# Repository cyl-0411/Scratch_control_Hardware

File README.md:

# Scratch_control_Hardware

	`Robotmaster`资源岛的控制器，需要控制一个舵机、一条LED灯带和一个红外传感器。
	
	主控：`STM32G030F6P6`，十分的廉价
	
	舵机：`MG995`

#### 更新日志：

2022/7/23

第一版比较拉，现在第二版准备不用中心板，直接将`MG995`、LED灯带和传感器接到主控板上。

此外会更新丝印，防止反插的情况。

2022/10/1

增加了几个去耦电容。

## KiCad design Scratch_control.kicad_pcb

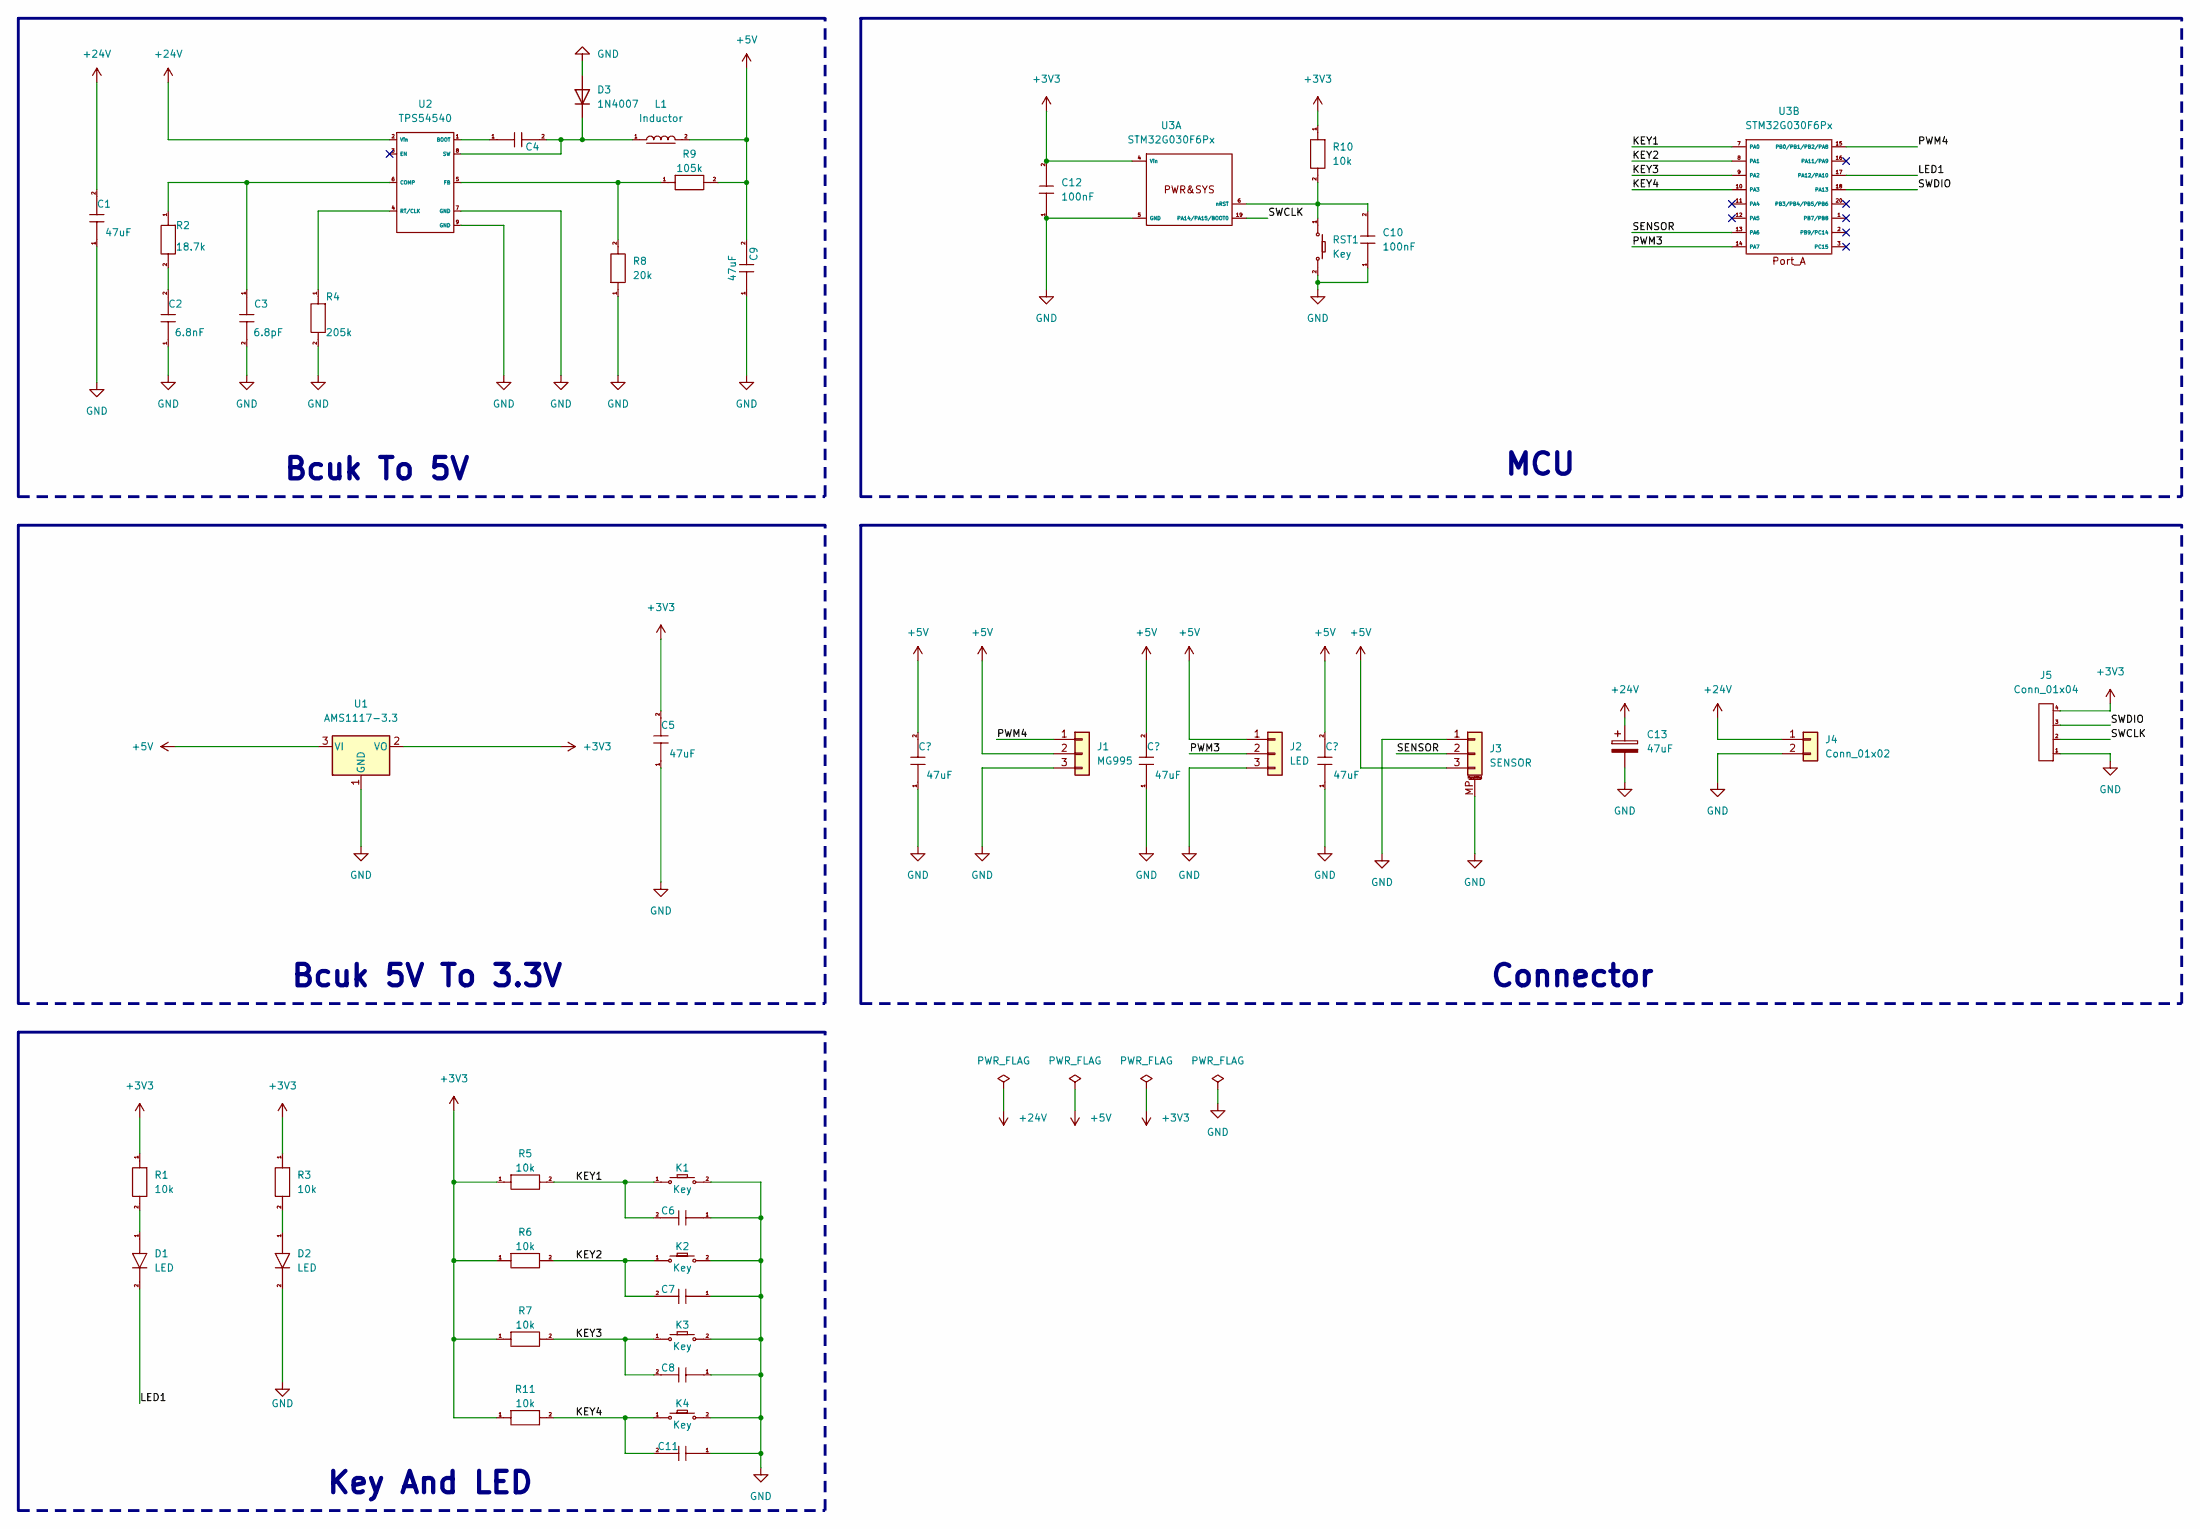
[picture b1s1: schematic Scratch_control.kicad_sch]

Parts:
C1: 47uF; C_0805_2012Metric
C2: 6.8nF; C_0603_1608Metric
C3: 6.8pF; C_0603_1608Metric
C4, C6, C7, C8, C10, C11, C12: 100nF; C_0603_1608Metric
C5, C9: 47uF; C_0603_1608Metric
C13: 47uF; CP_Elec_8x10
D1, D2: LED; LED_0603_1608Metric
D3: 1N4007; D_SMA
J1: MG995; PinHeader_1x03_P2.54mm_Horizontal
J2: LED; PinHeader_1x03_P2.54mm_Horizontal
J3: SENSOR; JST_GH_SM03B-GHS-TB_1x03-1MP_P1.25mm_Horizontal
J4: Conn_01x02; AMASS_XT30PW-M_1x02_P2.50mm_Horizontal
J5: Conn_01x04; PinHeader_1x04_P2.54mm_Horizontal
K1, K2, K3, K4: Key; SW_DIP_SPSTx01_Slide_6.7x4.1mm_W6.73mm_P2.54mm_LowProfile_J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
L1: Inductor; L_7.3x7.3_H4.5
R1, R3, R5, R6, R7, R10, R11: 10k; R_0603_1608Metric
R2: 18.7k; R_0603_1608Metric
R4: 205k; R_0603_1608Metric
R8: 20k; R_0603_1608Metric
R9: 105k; R_0603_1608Metric
RST1: Key; SW_DIP_SPSTx01_Slide_6.7x4.1mm_W6.73mm_P2.54mm_LowProfile_J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
U1: AMS1117-3.3; SOT-223-3_TabPin2
U2: TPS54540; HSOP-8-1EP_3.9x4.9mm_P1.27mm_EP2.41x3.1mm
U3: STM32G030F6Px; TSSOP-20_4.4x6.5mm_P0.65mm

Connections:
+3V3: C5.2, C12.2, J5.4, R1.1, R3.1, R5.1, R6.1, R7.1, R10.1, R11.1, U1.2 (VO), U3.4 (Vin)
+5V: C9.2, J1.2, J2.1, J3.3, L1.2, R9.2, U1.3 (VI); also elsewhere on the board
+24V: C1.2, C13.1, J4.1, U2.2 (Vin)
/KEY1: C6.2, K1.1, R5.2, U3.7 (PA0)
/KEY2: C7.2, K2.1, R6.2, U3.8 (PA1)
/KEY3: C8.2, K3.1, R7.2, U3.9 (PA2)
/KEY4: C11.2, K4.1, R11.2, U3.10 (PA3)
/LED1: D1.2, U3.17 (PA12/PA10)
/PWM3: J2.2, U3.14 (PA7)
/PWM4: J1.1, U3.15 (PB0/PB1/PB2/PA8)
/SENSOR: J3.2, U3.13 (PA6)
/SWCLK: J5.2, U3.19 (PA14/PA15/BOOT0)
/SWDIO: J5.3, U3.18 (PA13)
GND: C1.1, C2.1, C3.2, C5.1, C6.1, C7.1, C8.1, C9.1, C10.1, C11.1, C12.1, C13.2, D2.2, D3.2 (A), J1.3, J2.3, J3.1, J3.MP (MountPin), J4.2, J5.1, K1.2, K2.2, K3.2, K4.2, R4.2, R8.1, RST1.2, U1.1 (GND), U2.7 (GND), U2.9 (GND), U3.5 (GND); also elsewhere on the board
unnamed: C2.2, R2.2
unnamed: C3.1, R2.1, U2.6 (COMP)
unnamed: C4.1, U2.1 (BOOT)
unnamed: C4.2, D3.1 (K), L1.1, U2.8 (SW)
unnamed: C10.2, R10.2, RST1.1, U3.6 (nRST)
unnamed: D1.1, R1.2
unnamed: D2.1, R3.2
unnamed: R4.1, U2.4 (RT/CLK)
unnamed: R8.2, R9.1, U2.5 (FB)

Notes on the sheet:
Key And LED
MCU
Connector
Bcuk To 5V
Bcuk 5V To 3.3V

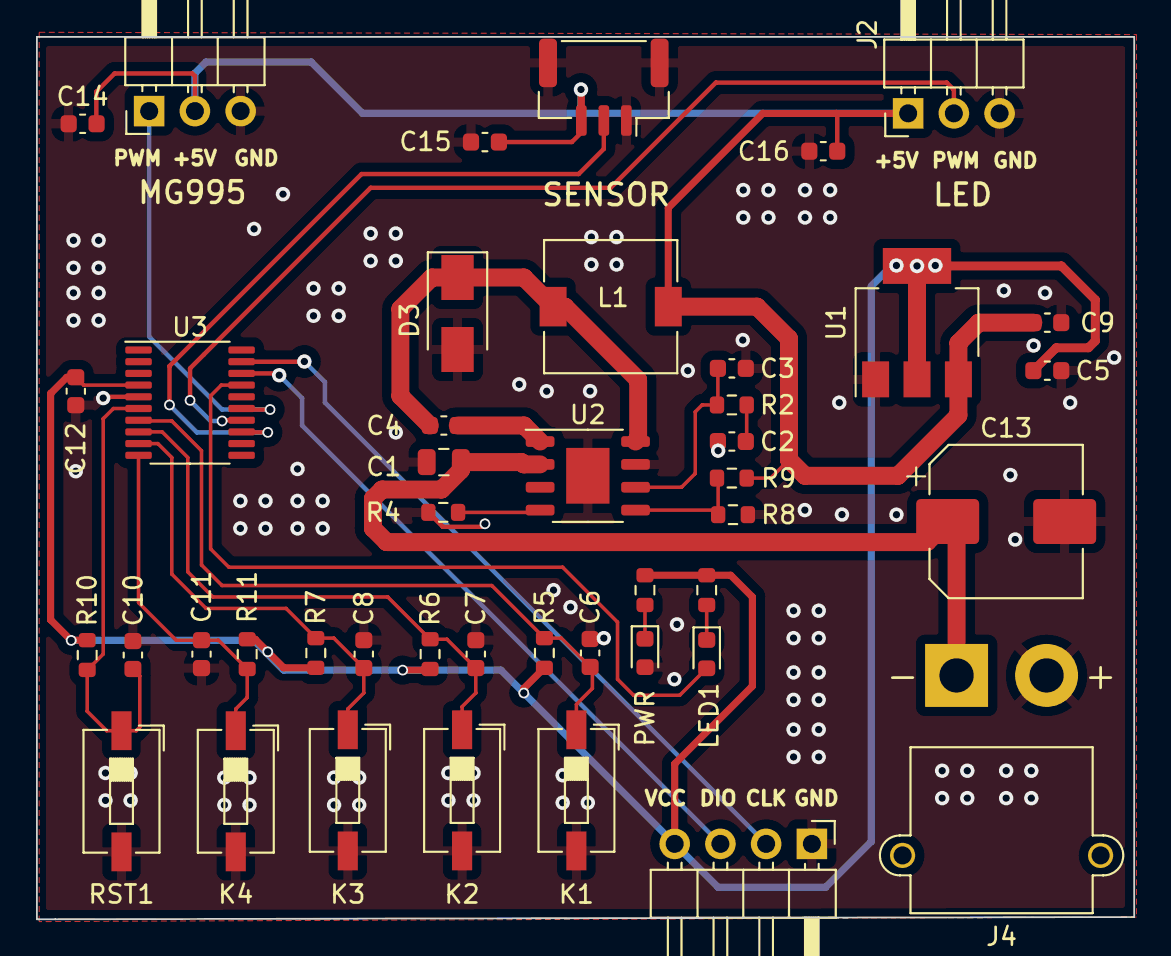
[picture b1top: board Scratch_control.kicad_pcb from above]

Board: 2 copper layers, 61.0 x 49.0 mm, 44 parts (0 on the bottom side), 23 nets.

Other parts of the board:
C14, C15, C16: 47uF; C_0603_1608Metric

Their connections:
+5V: C14.2, C15.2, C16.2; also elsewhere on the board
GND: C14.1, C15.1, C16.1; also elsewhere on the board

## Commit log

2022-07-23 first commit.The hardware of rm_scratch control.
2022-07-23 Update README.md.
2022-07-23 Update whole project.Delete some useless pin and so on....
2022-09-30 add some decoupling capacitors
